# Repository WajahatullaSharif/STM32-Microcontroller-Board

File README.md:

# DeskNode-F4: Desk Automation Node

**DeskNode-F4** is an intelligent, high-current desk automation controller designed to eliminate phantom standby power and manage workspace environments dynamically. Built around the **STM32F407VGT6** microcontroller, the board intercepts host sleep/wake signals to automatically switch power rails for major workspace appliances and custom peripherals.

---

## 📊 System Architecture Block Diagram

```mermaid
graph TD
    %% Styling Configuration
    classDef mcu fill:#1b4d3e,stroke:#333,stroke-width:1.5px,color:#fff;
    classDef power fill:#d4af37,stroke:#333,stroke-width:1px,color:#000;
    classDef peripheral fill:#e1f5fe,stroke:#0288d1,stroke-width:1px,color:#000;
    classDef external fill:#f5f5f5,stroke:#616161,stroke-width:1px,color:#000;

    %% Central PCBA
    subgraph DeskNode_F4 [DeskNode-F4]
        DEBUGGER[STM32F103 Debugger]:::mcu
        MCU[STM32F407 MCU]:::mcu
        ETH[DP83826 PHY]:::peripheral
        LED_DRV[LED Driver ~5A]:::peripheral
        SENSE[Shunt + Op-Amp]:::peripheral
        RELAY_DRV[Relay Drivers]:::peripheral
    end

    %% Left-Side Power Inputs
    USB_OTG[OTG USB]:::power
    USB_DEB[Debug USB]:::power

    %% External Systems
    subgraph Laptop_Host [Laptop Host]
        LAPTOP[Laptop PC]:::external
    end

    subgraph AC_Loads [AC Mains Loads]
        LOADS[Monitors/Speakers/Other]:::external
    end

    %% Invisible spacer layout trick to push AC Loads down
    Laptop_Host ~~~ AC_Loads

    %% Left-Side Power Routing Layout
    USB_OTG -->|Power Input| MCU
    USB_DEB --> DEBUGGER
    DEBUGGER -->|Debug/Power| MCU
    
    %% Right-Side Power Routing Layout
    12V[12V Adaptor]:::power -->|DC Jack| LED_DRV

    %% Communication & Interface Links
    LAPTOP -->|Ethernet Link| ETH
    ETH <-->|RMII| MCU
    LAPTOP -->|USB CDC| MCU

    %% Output Paths
    MCU -->|PWM| LED_DRV -->|JST| STRIP[RGB LED Strip]:::external
    STRIP -->|Return| SENSE -->|Analog| MCU
    MCU -->|GPIO| RELAY_DRV -->|Control| AC_Loads
```

---

## 🛠️ System Architecture Overview

The core of the system is a custom **4-layer PCB** configured with a high-integrity stackup (**Signal / GND / Power / Signal**) to isolate sensitive analog paths from high-power switching transients.

### Onboard Hardware Features
* **Microcontroller:** STM32F407 ARM Cortex-M4 operating with a high-performance clock tree to coordinate networking, USB stacks, and deterministic control loops.
* **Onboard Debugger:** Integrated STM32F103-based DAP-Link. This permits single-cable firmware flashing and debugging directly over the `Debug USB` port without requiring external programmers.
* **Networking Subsystem:** DP83826 Physical Layer (PHY) transceiver linked to the MCU via a low-pin-count **RMII (Reduced Media Independent Interface)** bus. It provides a dedicated pipeline for sending continuous telemetry and log metrics to an external server or logging application.
* **Dual Power Inputs:** Flexible bus powering options allow the system logic to run entirely off the `Debugger USB (5V)` line or the primary `OTG USB (5V)` interface.

### Peripheral Control & Telemetry Loops
* **High-Current LED Driver:** A dedicated ~5A PWM driver stage capable of dimming and driving dense RGB LED strips utilized for monitor backlighting.
* **Current Telemetry (Shunt + Op-Amp):** A low-side inline current shunt paired with a precision operational amplifier provides analog current sensing feedback directly to the MCU's internal ADC. This ensures overload protection and active power calculation.
* **Relay Driver Array:** Low-voltage GPIO pins drive transistor/optocoupler stages to switch external heavy-duty AC relay modules safely.

---

## 🔄 Sequence of Operation

The system functions on a deterministic host-state monitoring loop via a virtual COM port over USB:

| Laptop State | USB CDC Pipeline | DeskNode-F4 Action |
| :--- | :--- | :--- |
| **Laptop Wakes** | Sends `"WAKE"` Token | 1. Latches AC Relays **ON** <br> 2. Ramps up Monitor LED Strip and Speakers |
| **Laptop Sleeps** | CDC Connection Drops | 1. Unlatches AC Relays **OFF** <br> 2. Cuts LED Strip Power |

### 1. The Wake Sequence (Power-On)
1. The host laptop wakes from standby or a sleep state.
2. An automation daemon running on the host detects the system state change and establishes a **USB CDC (Communications Device Class)** virtual serial connection.
3. The host transmits a configuration/activation token to the `DeskNode-F4` over USB.
4. The MCU immediately asserts its control GPIOs:
    * **Relay Output Pins** transition to high, latching the AC relay modules to deliver mains power simultaneously to **Monitor 1, Monitor 2, the Laptop Power Adaptor, and the Home Theatre System**.
    * **PWM Driver** initializes to ramp up the RGB backlight strip to the user's preferred brightness level via the onboard JST connection.

### 2. Continuous Monitoring State
* While active, the board uses the **DP83826 Ethernet PHY** to broadcast runtime diagnostics (uptime, temperature, and power drawing conditions) back to the laptop's logging software.
* The internal ADC continuously updates using the operational amplifier feedback loop across the shunt resistor to verify the current draw of the 5A LED string remains within a safe operating safe area (SOA).

### 3. The Sleep Sequence (Zero-Standby Power)
1. The host laptop enters a low-power sleep mode or is shut down.
2. The active USB CDC bus is dropped or broadcasts a graceful shutdown command packet.
3. Upon detecting the drop in the USB connection state, the `STM32F407` executes an emergency environment teardown:
    * All **GPIO Relay Driver lines** drop low, physically disconnecting the mains AC power lines. This drops the idle standby current consumption of the entire desk setup (monitors, sound systems, bricks) down to **absolute zero**.
    * The LED driver PWM is pulled to a 0% duty cycle, turning off the backlight completely.
    * The board drops into a low-power listening loop, drawing minimal parasitic power through the connected USB line until the next wake event.

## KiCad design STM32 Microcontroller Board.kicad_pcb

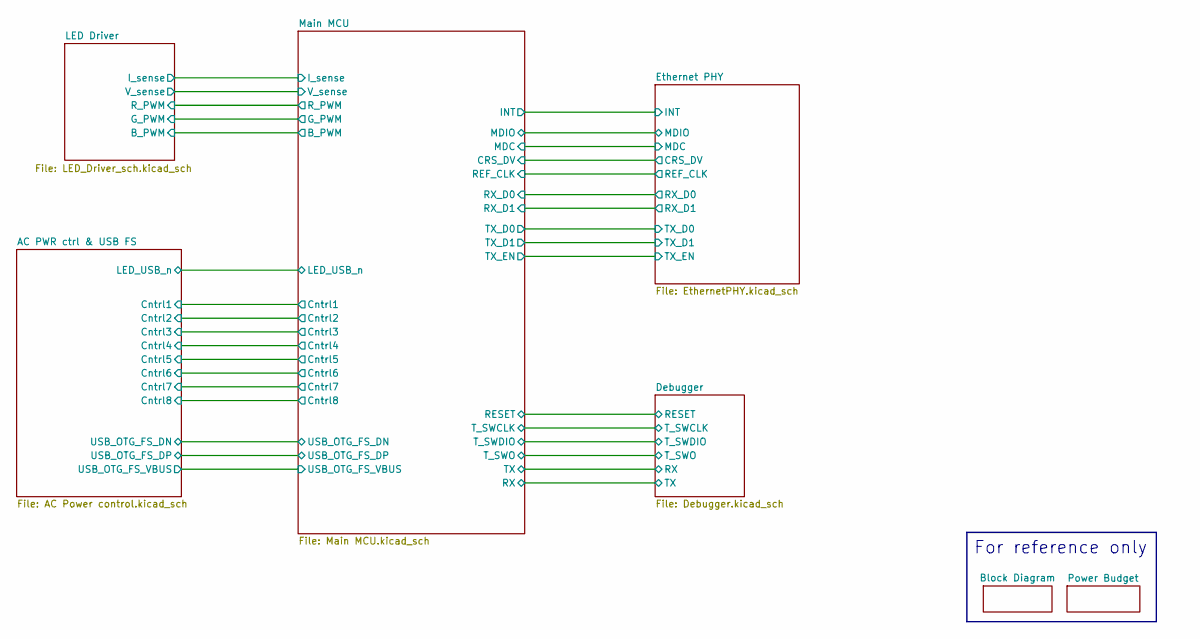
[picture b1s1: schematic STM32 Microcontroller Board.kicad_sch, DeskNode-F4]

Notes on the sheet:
For reference only

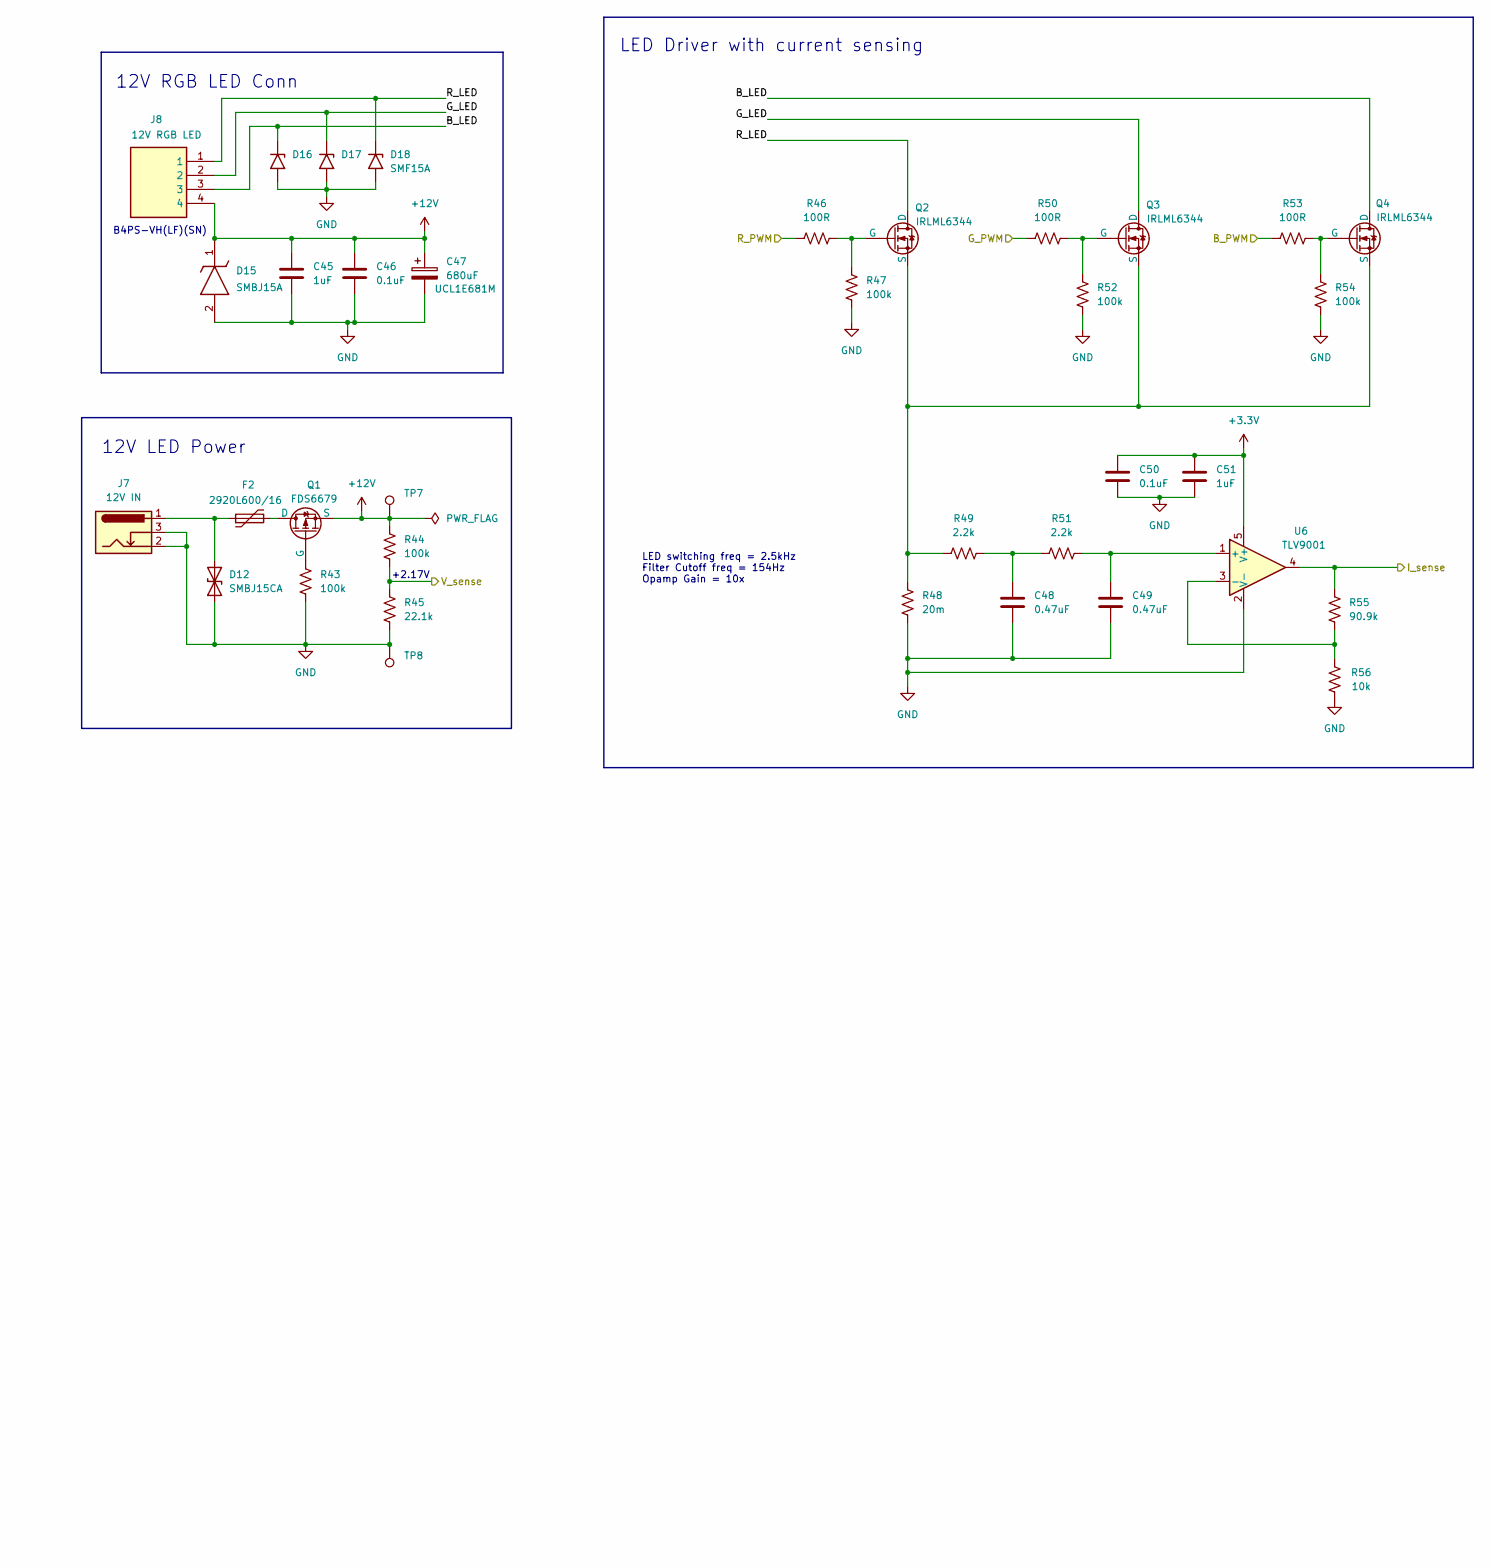
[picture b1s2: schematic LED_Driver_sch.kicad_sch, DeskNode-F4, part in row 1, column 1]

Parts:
C45: 1uF; C_0603_1608Metric; MPN CC0603KRX7R9BB105
C46: 0.1uF; C_0603_1608Metric; MPN C0603C104K5RACTU
C47: 680uF; UCL1E681MNL1GS; MPN UCL1E681MNL1GS
C48, C49: 0.47uF; C_0603_1608Metric; MPN CL10B474KA8NFNC
C50: 0.1uF; C_0402_1005Metric; MPN GRM155R71A104KA01D
C51: 1uF; C_0603_1608Metric; MPN CL10B105KP8NNNC
D12: SMBJ15CA; SMBJ15A; MPN SMBJ15CA
D15: SMBJ15A; Mouser Part Number 576-SMBJ15A
D16, D17, D18: SMF15A; D_SMF; MPN SMF15A
F2: Polyfuse; Fuse_2920_7451Metric; MPN 2920L600/16MR
J7: 12V IN; BarrelJack_Horizontal
J8: 12V RGB LED; B4PS-VH; Mouser Part Number 306-B4PS-VHLFSN
Q1: PMOS; SOIC-8_5.3x5.3mm_P1.27mm; Manufacturer_Part_Number FDS6679
Q2, Q3, Q4: NMOS; SOT-23; MPN IRLML6344TRPBF
R43, R44, R47, R52, R54: 100k; R_0603_1608Metric; MPN RC0603FR-07100KL
R45: 22.1k; R_0603_1608Metric; MPN RC0603FR-0722K1L
R46, R50, R53: 100R; R_0603_1608Metric; MPN RC0603FR-07100RL
R48: 20m; R_2512_6332Metric; MPN CRA2512-FZ-R020ELF
R49, R51: 2.2k; R_0603_1608Metric; MPN RC0603FR-072K2L
R55: 90.9k; R_0603_1608Metric; MPN RC0603FR-0790K9L
R56: 10k; R_0603_1608Metric; MPN RC0603FR-0710KL
TP7, TP8: TestPoint; TestPoint_Keystone_5000-5004_Miniature; MPN 5001
U6: TLV9001TIDCKR; SOT-353_SC-70-5; MPN TLV9001TIDCKR

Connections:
+3.3V: C50.1, C51.1, U6.5 (V+); also elsewhere on the board
+12V: C45.1, C46.1, C47.1, D15.1 (K), J8.4, Q1.2 (S), R44.1, TP7.1; also elsewhere on the board
/LED Driver/B_LED: D16.1 (A1), J8.3, Q4.1 (D)
/LED Driver/B_PWM: R53.1; also elsewhere on the board
/LED Driver/G_LED: D17.1 (A1), J8.2, Q3.1 (D)
/LED Driver/G_PWM: R50.1; also elsewhere on the board
/LED Driver/I_sense: R55.2, U6.4; also elsewhere on the board
/LED Driver/R_LED: D18.1 (A1), J8.1, Q2.1 (D)
/LED Driver/R_PWM: R46.1; also elsewhere on the board
/Main MCU/PB1: R44.2, R45.1; also elsewhere on the board
GND: C45.2, C46.2, C47.2, C48.2, C49.1, C50.2, C51.2, D12.1 (A1), D15.2 (A), D16.2 (A2), D17.2 (A2), D18.2 (A2), J7.2, J7.3, R43.2, R45.2, R47.2, R48.2, R52.2, R54.2, R56.1, TP8.1, U6.2 (V-); also elsewhere on the board
unnamed: C48.1, R49.2, R51.1
unnamed: D12.2 (A2), F2.1, J7.1
unnamed: F2.2, Q1.3 (D)
unnamed: Q1.1 (G), R43.1
unnamed: Q2.2 (G), R46.2, R47.1
unnamed: Q2.3 (S), Q3.3 (S), Q4.3 (S), R48.1, R49.1
unnamed: Q3.2 (G), R50.2, R52.1
unnamed: Q4.2 (G), R53.2, R54.1
unnamed: C49.2, R51.2, U6.1 (+)
unnamed: R55.1, R56.2, U6.3 (-)

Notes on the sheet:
+2.17V
LED switching freq = 2.5kHz Filter Cutoff freq = 154Hz Opamp Gain = 10x
12V LED Power
12V RGB LED Conn
LED Driver with current sensing
B4PS-VH(LF)(SN)

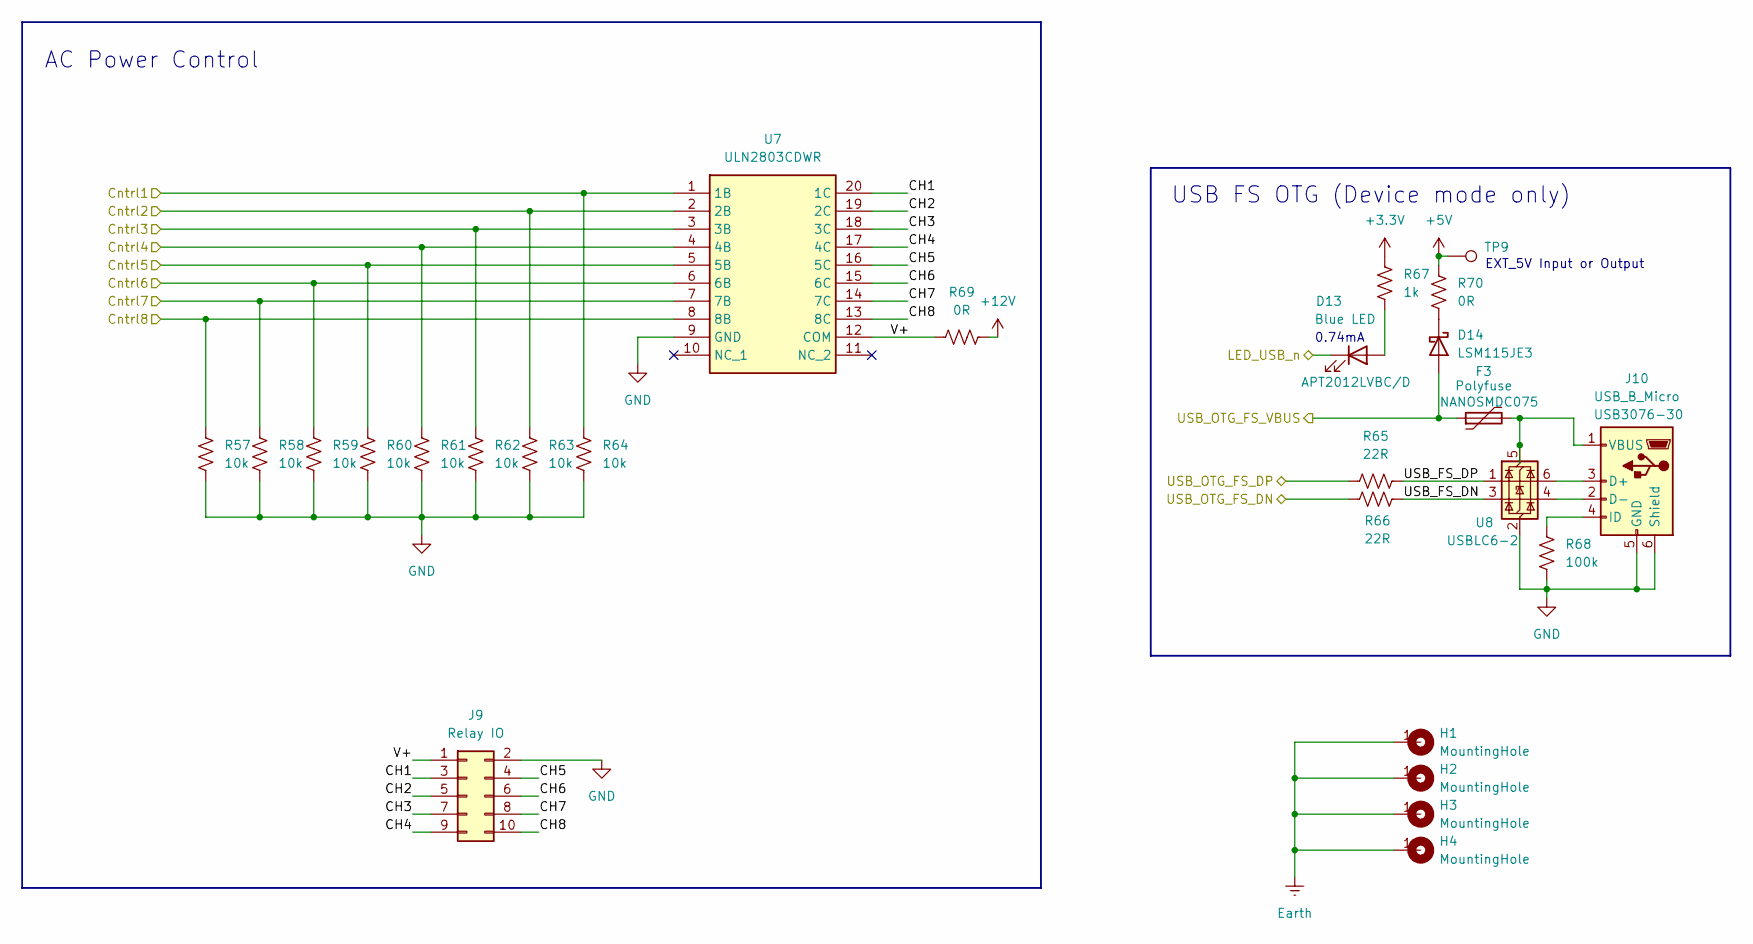
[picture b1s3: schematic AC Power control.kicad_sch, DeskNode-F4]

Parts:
D13: Blue LED; LED_0805_2012Metric; MPN APT2012LVBC/D
D14: LSM115JE3; D_SMB; MPN LSM115JE3-TR13
F3: Polyfuse; Fuse_1206_3216Metric; MPN NANOSMDC075F-2
H1, H2, H3, H4: MountingHole; MountingHole_3.2mm_M3_Pad
J9: Relay IO; PinHeader_2x05_P2.54mm_Vertical
J10: USB_B_Micro; USB_Micro-B_GCT_USB3076-30-A; MPN USB3076-30-A
R57, R58, R59, R60, R61, R62, R63, R64: 10k; R_0603_1608Metric; MPN RC0603FR-0710KL
R65, R66: 22R; R_0603_1608Metric; MPN RC0603FR-0722RL
R67: 1k; R_0603_1608Metric; MPN RC0603FR-071KL
R68: 100k; R_0603_1608Metric; MPN RC0603FR-07100KL
R69, R70: 0R; R_0603_1608Metric; MPN RC0603JR-070RL
TP9: TestPoint; TestPoint_Keystone_5000-5004_Miniature; MPN 5001
U7: ULN2803CDWR; Mouser Part Number 595-ULN2803CDWR
U8: USBLC6-2; SOT-23-6; MPN USBLC6-2SC6

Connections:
+3.3V: R67.1; also elsewhere on the board
+5V: R70.2, TP9.1; also elsewhere on the board
+12V: R69.2; also elsewhere on the board
/AC PWR ctrl & USB FS/CH1: J9.3, U7.20 (1C)
/AC PWR ctrl & USB FS/CH2: J9.5, U7.19 (2C)
/AC PWR ctrl & USB FS/CH3: J9.7, U7.18 (3C)
/AC PWR ctrl & USB FS/CH4: J9.9, U7.17 (4C)
/AC PWR ctrl & USB FS/CH5: J9.4, U7.16 (5C)
/AC PWR ctrl & USB FS/CH6: J9.6, U7.15 (6C)
/AC PWR ctrl & USB FS/CH7: J9.8, U7.14 (7C)
/AC PWR ctrl & USB FS/CH8: J9.10, U7.13 (8C)
/AC PWR ctrl & USB FS/Cntrl1: R64.1, U7.1 (1B); also elsewhere on the board
/AC PWR ctrl & USB FS/Cntrl2: R63.1, U7.2 (2B); also elsewhere on the board
/AC PWR ctrl & USB FS/Cntrl3: R62.1, U7.3 (3B); also elsewhere on the board
/AC PWR ctrl & USB FS/Cntrl4: R61.1, U7.4 (4B); also elsewhere on the board
/AC PWR ctrl & USB FS/Cntrl5: R60.1, U7.5 (5B); also elsewhere on the board
/AC PWR ctrl & USB FS/Cntrl6: R59.1, U7.6 (6B); also elsewhere on the board
/AC PWR ctrl & USB FS/Cntrl7: R58.1, U7.7 (7B); also elsewhere on the board
/AC PWR ctrl & USB FS/Cntrl8: R57.1, U7.8 (8B); also elsewhere on the board
/AC PWR ctrl & USB FS/LED_USB_n: D13.1 (K); also elsewhere on the board
/AC PWR ctrl & USB FS/USB_FS_DN: R66.2, U8.3 (I/O2)
/AC PWR ctrl & USB FS/USB_FS_DP: R65.1, U8.1 (I/O1)
/AC PWR ctrl & USB FS/USB_OTG_FS_DN: R66.1; also elsewhere on the board
/AC PWR ctrl & USB FS/USB_OTG_FS_DP: R65.2; also elsewhere on the board
/AC PWR ctrl & USB FS/USB_OTG_FS_VBUS: D14.2 (A), F3.1; also elsewhere on the board
/AC PWR ctrl & USB FS/V+: J9.1, R69.1, U7.12 (COM)
Earth: H1.1, H2.1, H3.1, H4.1; also elsewhere on the board
GND: J9.2, J10.5 (GND), J10.6 (Shield), R57.2, R58.2, R59.2, R60.2, R61.2, R62.2, R63.2, R64.2, R68.1, U7.9 (GND), U8.2 (GND); also elsewhere on the board
unnamed: D13.2 (A), R67.2
unnamed: D14.1 (K), R70.1
unnamed: J10.3 (D+), U8.6 (I/O1)
unnamed: J10.2 (D-), U8.4 (I/O2)
unnamed: J10.4 (ID), R68.2
unnamed: F3.2, J10.1 (VBUS), U8.5 (VBUS)

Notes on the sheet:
USB FS OTG (Device mode only)
EXT_5V Input or Output
AC Power Control
0.74mA

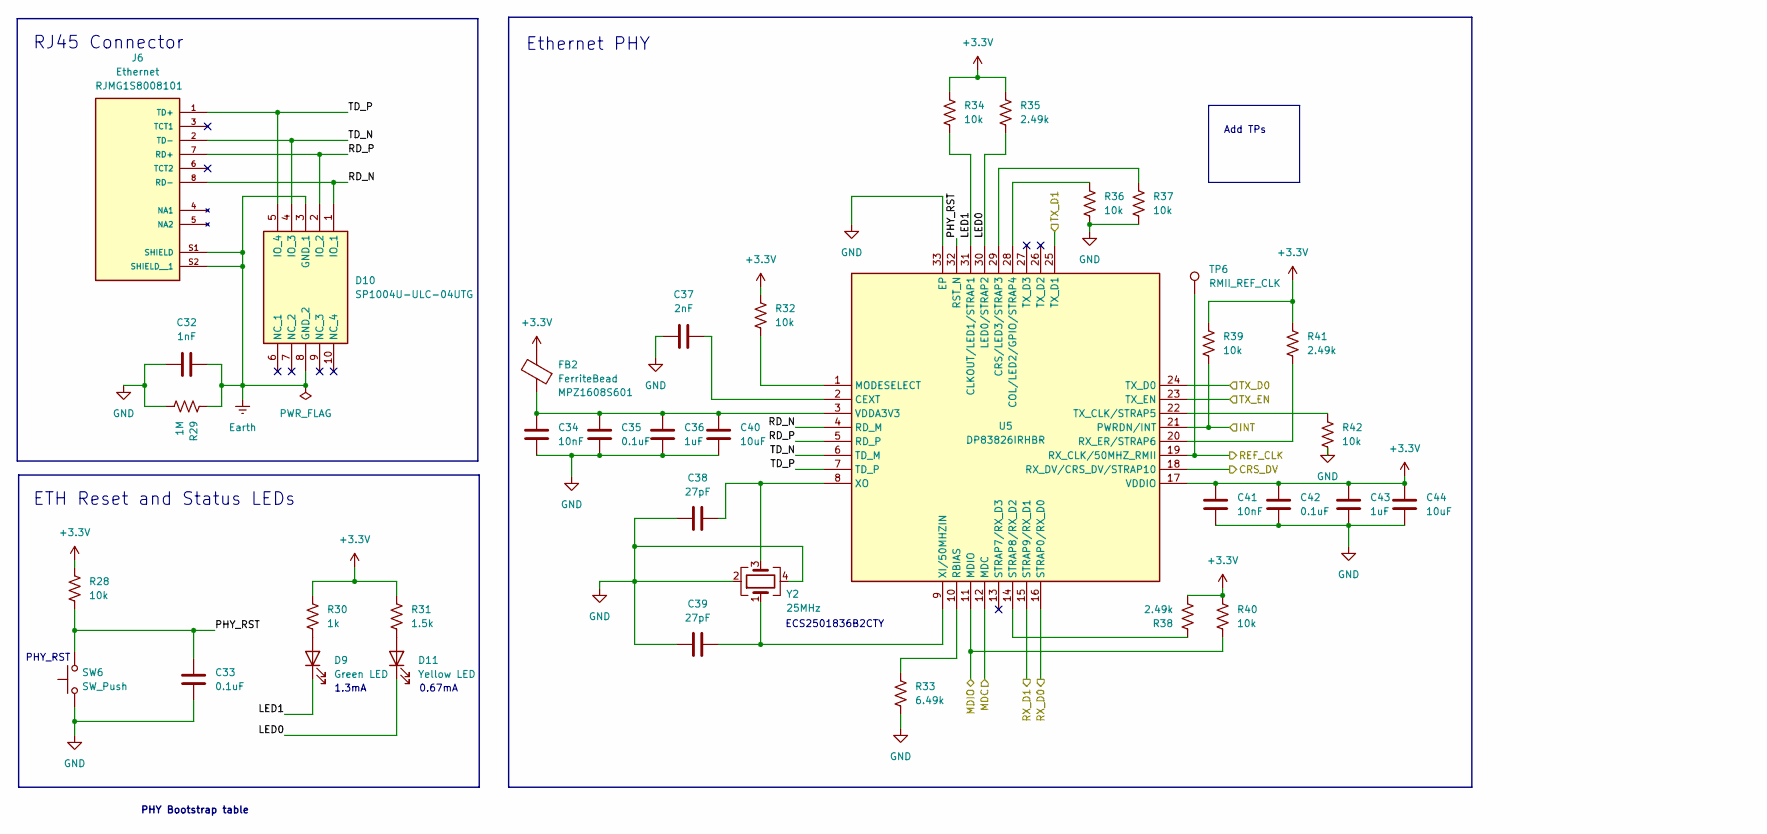
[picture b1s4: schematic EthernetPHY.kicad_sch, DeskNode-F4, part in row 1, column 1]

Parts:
C32: 1nF; C_1206_3216Metric; MPN CC1206KKX7RDBB102
C33, C35, C42: 0.1uF; C_0402_1005Metric; MPN GRM155R71A104KA01D
C34, C41: 10nF; C_0402_1005Metric; MPN GRM155R71E103KA01D
C36, C43: 1uF; C_0603_1608Metric; MPN CL10B105KP8NNNC
C37: 2nF; C_0603_1608Metric; MPN GRM1885C1H202JA01D
C38, C39: 27pF; C_0603_1608Metric; MPN CL10C270JB8NNNC
C40, C44: 10uF; C_0805_2012Metric; Manufacturer_Part_Number GRM21BR71A106KA73L
D9: Green LED; LED_0805_2012Metric; MPN APT2012CGCK
D10: SP1004U-ULC-04UTG; ESD8104MUTAG; MPN SP1004U-ULC-04UTG
D11: Yellow LED; LED_0805_2012Metric; MPN APT2012SYCK
FB2: FerriteBead; L_0603_1608Metric; MPN MPZ1608S601ATA00
J6: Ethernet; AMPHENOL_RJMG1S8008101BR; PARTREV A
R28, R32, R34, R36, R37, R39, R40, R42: 10k; R_0603_1608Metric; MPN RC0603FR-0710KL
R29: 1M; R_0603_1608Metric; MPN RC0603FR-071ML
R30: 1k; R_0603_1608Metric; MPN RC0603FR-071KL
R31: 1.5k; R_0603_1608Metric; MPN RC0603FR-071K5L
R33: 6.49k; R_0603_1608Metric; MPN RC0603FR-076K49L
R35, R38, R41: 2.49k; R_0603_1608Metric; MPN RC0603FR-072K49L
SW6: SW_Push; SW_SPST_PTS645Sx43SMTR92; MPN SWT0310-043016GSA
TP6: RMII_REF_CLK; TestPoint_Pad_D1.0mm
U5: DP83826IRHBR; QFN50P500X500X100-33N-D; Mouser Part Number 595-DP83826IRHBR
Y2: 25MHz; ECS2501836B2CTYTR; Mouser Part Number 520-250-18-36B2CTYTR

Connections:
+3.3V: C41.1, C42.1, C43.1, C44.1, FB2.2, R28.1, R30.1, R31.2, R32.1, R34.1, R35.1, R38.1, R39.1, R40.1, R41.1, U5.17 (VDDIO); also elsewhere on the board
/Ethernet PHY/CRS_DV: U5.18 (RX_DV/CRS_DV/STRAP10); also elsewhere on the board
/Ethernet PHY/INT: R39.2, U5.21 (PWRDN/INT); also elsewhere on the board
/Ethernet PHY/LED0: D11.1 (K), R35.2, U5.30 (LED0/STRAP2)
/Ethernet PHY/LED1: D9.1 (K), R34.2, U5.31 (CLKOUT/LED1/STRAP1)
/Ethernet PHY/MDC: U5.12 (MDC); also elsewhere on the board
/Ethernet PHY/MDIO: R40.2, U5.11 (MDIO); also elsewhere on the board
/Ethernet PHY/PHY_RST: C33.1, R28.2, SW6.2, U5.32 (RST_N)
/Ethernet PHY/RD_N: D10.1 (IO_1), J6.8 (RD-), U5.4 (RD_M)
/Ethernet PHY/RD_P: D10.2 (IO_2), J6.7 (RD+), U5.5 (RD_P)
/Ethernet PHY/REF_CLK: TP6.1, U5.19 (RX_CLK/50MHZ_RMII); also elsewhere on the board
/Ethernet PHY/RX_D0: U5.16 (STRAP0/RX_D0); also elsewhere on the board
/Ethernet PHY/RX_D1: U5.15 (STRAP9/RX_D1); also elsewhere on the board
/Ethernet PHY/TD_N: D10.4 (IO_3), J6.2 (TD-), U5.6 (TD_M)
/Ethernet PHY/TD_P: D10.5 (IO_4), J6.1 (TD+), U5.7 (TD_P)
/Ethernet PHY/TX_D0: U5.24 (TX_D0); also elsewhere on the board
/Ethernet PHY/TX_D1: U5.25 (TX_D1); also elsewhere on the board
/Ethernet PHY/TX_EN: U5.23 (TX_EN); also elsewhere on the board
Earth: C32.2, D10.3 (GND_1), D10.8 (GND_2), J6.S1 (SHIELD), J6.S2 (SHIELD__1), R29.2; also elsewhere on the board
GND: C32.1, C33.2, C34.2, C35.2, C36.2, C37.1, C38.1, C39.1, C40.2, C41.2, C42.2, C43.2, C44.2, R29.1, R33.1, R36.2, R37.2, R42.2, SW6.1, U5.33 (EP), Y2.2, Y2.4; also elsewhere on the board
unnamed: D9.2 (A), R30.2
unnamed: D11.2 (A), R31.1
unnamed: C37.2, U5.2 (CEXT)
unnamed: R36.1, U5.28 (COL/LED2/GPIO/STRAP4)
unnamed: R37.1, U5.29 (CRS/LED3/STRAP3)
unnamed: R32.2, U5.1 (MODESELECT)
unnamed: R33.2, U5.10 (RBIAS)
unnamed: R41.2, U5.20 (RX_ER/STRAP6)
unnamed: R38.2, U5.14 (STRAP8/RX_D2)
unnamed: R42.1, U5.22 (TX_CLK/STRAP5)
unnamed: C34.1, C35.1, C36.1, C40.1, FB2.1, U5.3 (VDDA3V3)
unnamed: C39.2, U5.9 (XI/50MHZIN), Y2.1
unnamed: C38.2, U5.8 (XO), Y2.3

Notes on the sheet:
0.67mA
Add TPs
Ethernet PHY
ECS2501836B2CTY
PHY Bootstrap table
RJ45 Connector
1.3mA
PHY_RST
ETH Reset and Status LEDs

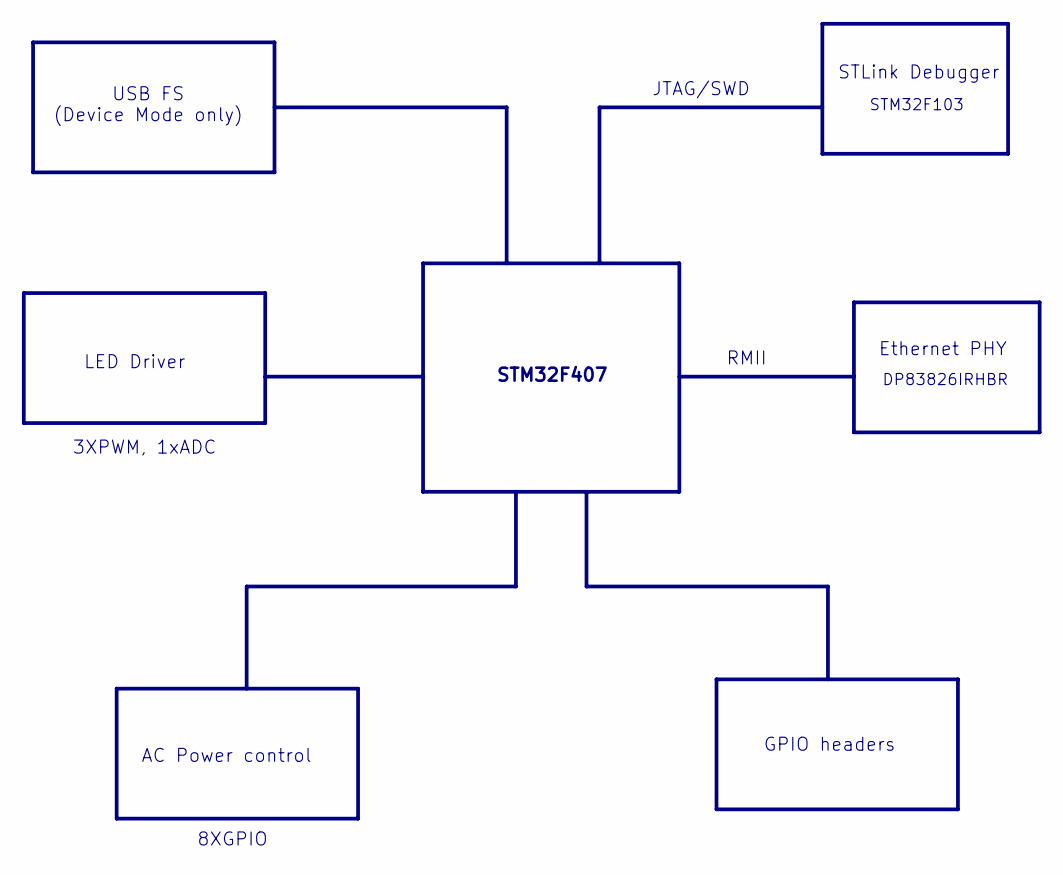
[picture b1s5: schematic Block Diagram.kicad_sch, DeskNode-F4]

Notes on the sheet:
DP83826IRHBR
STLink Debugger
LED Driver
JTAG/SWD
STM32F407
USB FS (Device Mode only)
GPIO headers
3XPWM, 1xADC
8XGPIO
STM32F103
Ethernet PHY
AC Power control
RMII

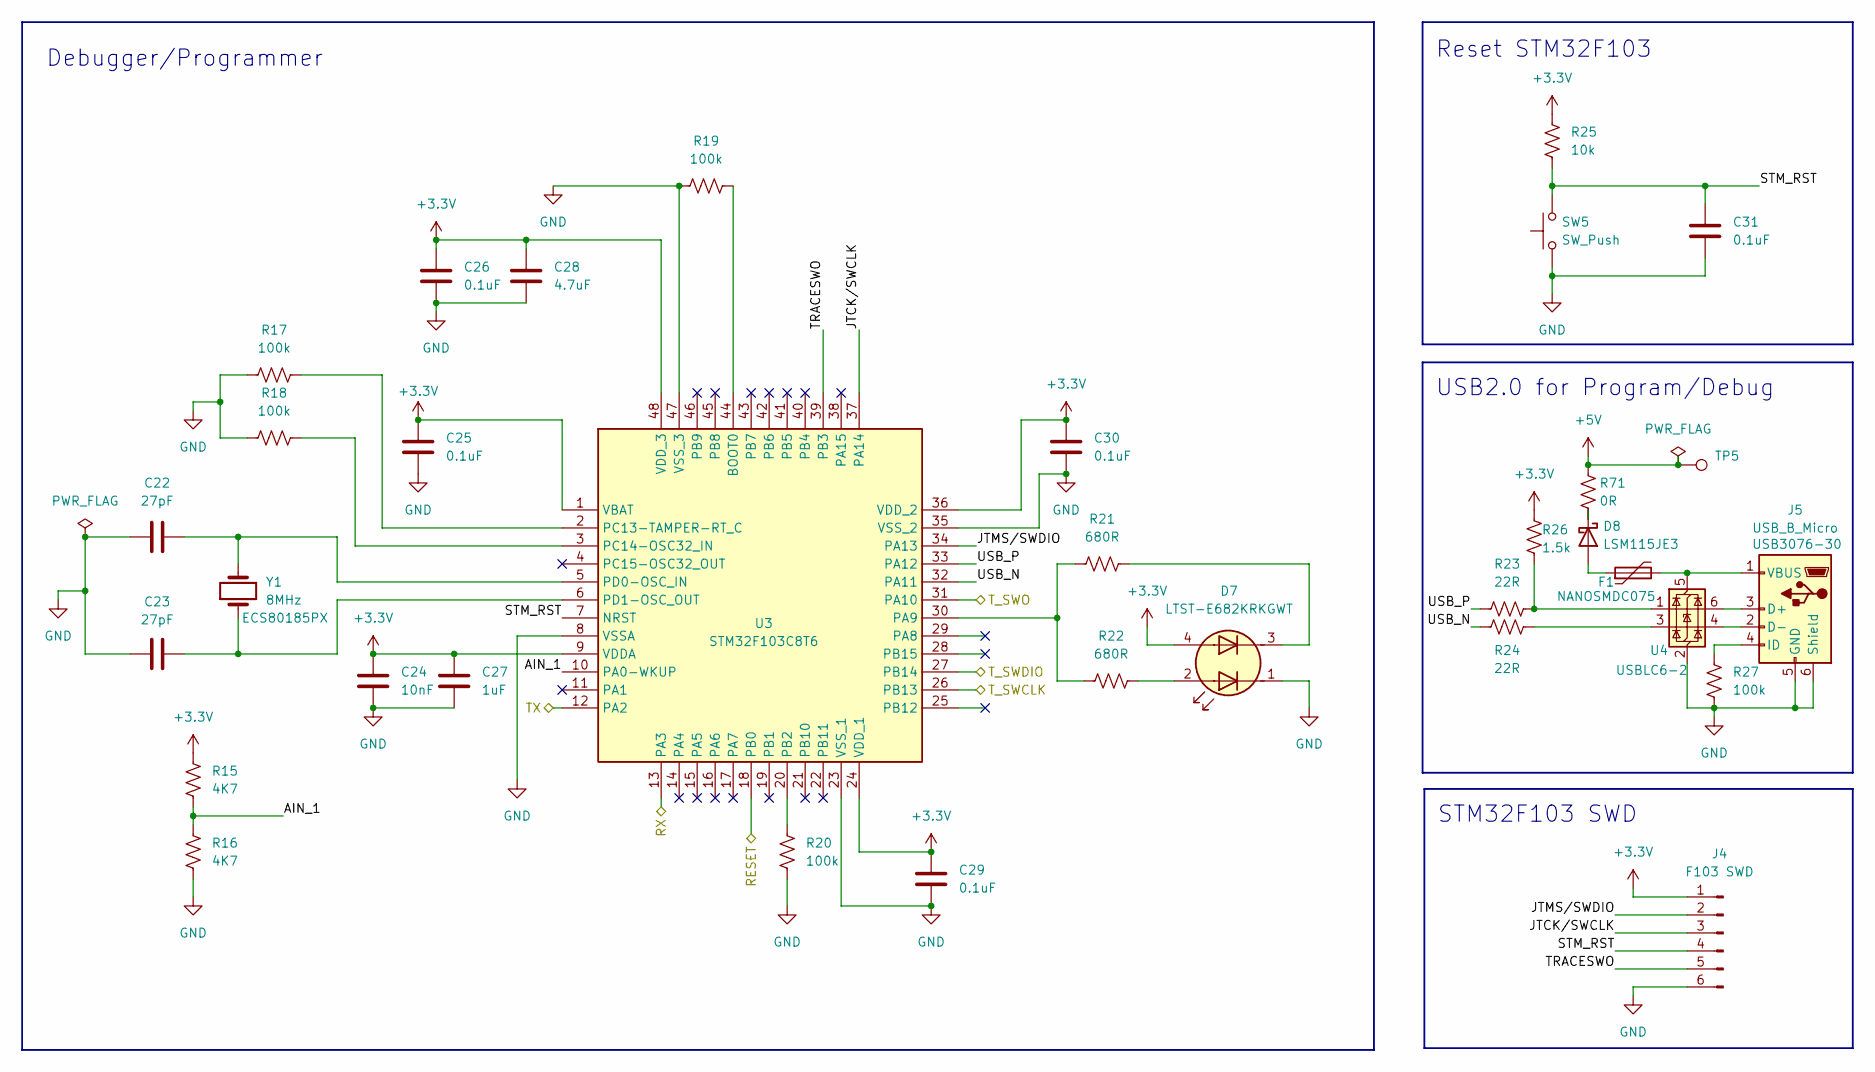
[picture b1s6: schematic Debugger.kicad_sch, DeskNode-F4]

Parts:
C22, C23: 27pF; C_0603_1608Metric; MPN CL10C270JB8NNNC
C24: 10nF; C_0402_1005Metric; MPN GRM155R71E103KA01D
C25, C26, C29, C30, C31: 0.1uF; C_0402_1005Metric; MPN GRM155R71A104KA01D
C27: 1uF; C_0603_1608Metric; MPN CL10B105KP8NNNC
C28: 4.7uF; C_0805_2012Metric; MPN GRM21BR71C475KE51L
D7: LTST-E682KRKGWT; LTSTE683RGBW; MPN LTST-E682KRKGWT
D8: LSM115JE3; D_SMB; MPN LSM115JE3-TR13
F1: Polyfuse; Fuse_1206_3216Metric; MPN NANOSMDC075F-2
J4: F103 SWD; PinHeader_1x06_P2.54mm_Vertical
J5: USB_B_Micro; USB_Micro-B_GCT_USB3076-30-A; MPN USB3076-30-A
R15, R16: 4K7; R_0603_1608Metric; MPN RC0603FR-074K7L
R17, R18, R19, R20, R27: 100k; R_0603_1608Metric; MPN RC0603FR-07100KL
R21, R22: 680R; R_0603_1608Metric; MPN RC0603FR-07680RL
R23, R24: 22R; R_0603_1608Metric; MPN RC0603FR-0722RL
R25: 10k; R_0603_1608Metric; MPN RC0603FR-0710KL
R26: 1.5k; R_0603_1608Metric; MPN RC0603FR-071K5L
R71: 0R; R_0603_1608Metric; MPN RC0603JR-070RL
SW5: SW_Push; SW_SPST_PTS645Sx43SMTR92; MPN SWT0310-043016GSA
TP5: TestPoint; TestPoint_Keystone_5000-5004_Miniature; MPN 5001
U3: STM32F103C8T6; QFP50P900X900X160-48N; Mouser Part Number 511-STM32F103C8T6
U4: USBLC6-2; SOT-23-6; MPN USBLC6-2SC6
Y1: 8MHz; Crystal_HC49-4H_Vertical; MPN ECS-80-18-5PX-TR

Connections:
+3.3V: C24.1, C25.1, C26.1, C27.1, C28.1, C29.1, C30.1, D7.4 (A2), J4.1, R15.2, R25.1, R26.1, U3.1 (VBAT), U3.9 (VDDA), U3.24 (VDD_1), U3.36 (VDD_2), U3.48 (VDD_3); also elsewhere on the board
+5V: R71.2, TP5.1; also elsewhere on the board
/Debugger/AIN_1: R15.1, R16.2, U3.10 (PA0-WKUP)
/Debugger/JTCK/SWCLK: J4.3, U3.37 (PA14)
/Debugger/JTMS/SWDIO: J4.2, U3.34 (PA13)
/Debugger/RX: U3.13 (PA3); also elsewhere on the board
/Debugger/STM_RST: C31.1, J4.4, R25.2, SW5.2, U3.7 (NRST)
/Debugger/TRACESWO: J4.5, U3.39 (PB3)
/Debugger/TX: U3.12 (PA2); also elsewhere on the board
/Debugger/USB_N: R24.1, U3.32 (PA11)
/Debugger/USB_P: R23.2, U3.33 (PA12)
/Main MCU/RESET: U3.18 (PB0); also elsewhere on the board
/Main MCU/T_SWCLK: U3.26 (PB13); also elsewhere on the board
/Main MCU/T_SWDIO: U3.27 (PB14); also elsewhere on the board
/Main MCU/T_SWO: U3.31 (PA10); also elsewhere on the board
GND: C22.1, C23.1, C24.2, C25.2, C26.2, C27.2, C28.2, C29.2, C30.2, C31.2, D7.1 (K1), J4.6, J5.5 (GND), J5.6 (Shield), R16.1, R17.1, R18.1, R19.1, R20.2, R27.1, SW5.1, U3.8 (VSSA), U3.23 (VSS_1), U3.35 (VSS_2), U3.47 (VSS_3), U4.2 (GND); also elsewhere on the board
unnamed: D7.2 (A1), R22.2
unnamed: D7.3 (K2), R21.2
unnamed: D8.2 (A), F1.1
unnamed: D8.1 (K), R71.1
unnamed: J5.3 (D+), U4.6 (I/O1)
unnamed: J5.2 (D-), U4.4 (I/O2)
unnamed: J5.4 (ID), R27.2
unnamed: F1.2, J5.1 (VBUS), U4.5 (VBUS)
unnamed: R23.1, R26.2, U4.1 (I/O1)
unnamed: R24.2, U4.3 (I/O2)
unnamed: R19.2, U3.44 (BOOT0)
unnamed: R21.1, R22.1, U3.30 (PA9)
unnamed: R20.1, U3.20 (PB2)
unnamed: R17.2, U3.2 (PC13-TAMPER-RT_C)
unnamed: R18.2, U3.3 (PC14-OSC32_IN)
unnamed: C22.2, U3.5 (PD0-OSC_IN), Y1.2
unnamed: C23.2, U3.6 (PD1-OSC_OUT), Y1.1

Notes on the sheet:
STM32F103 SWD
USB2.0 for Program/Debug
Reset STM32F103
Debugger/Programmer

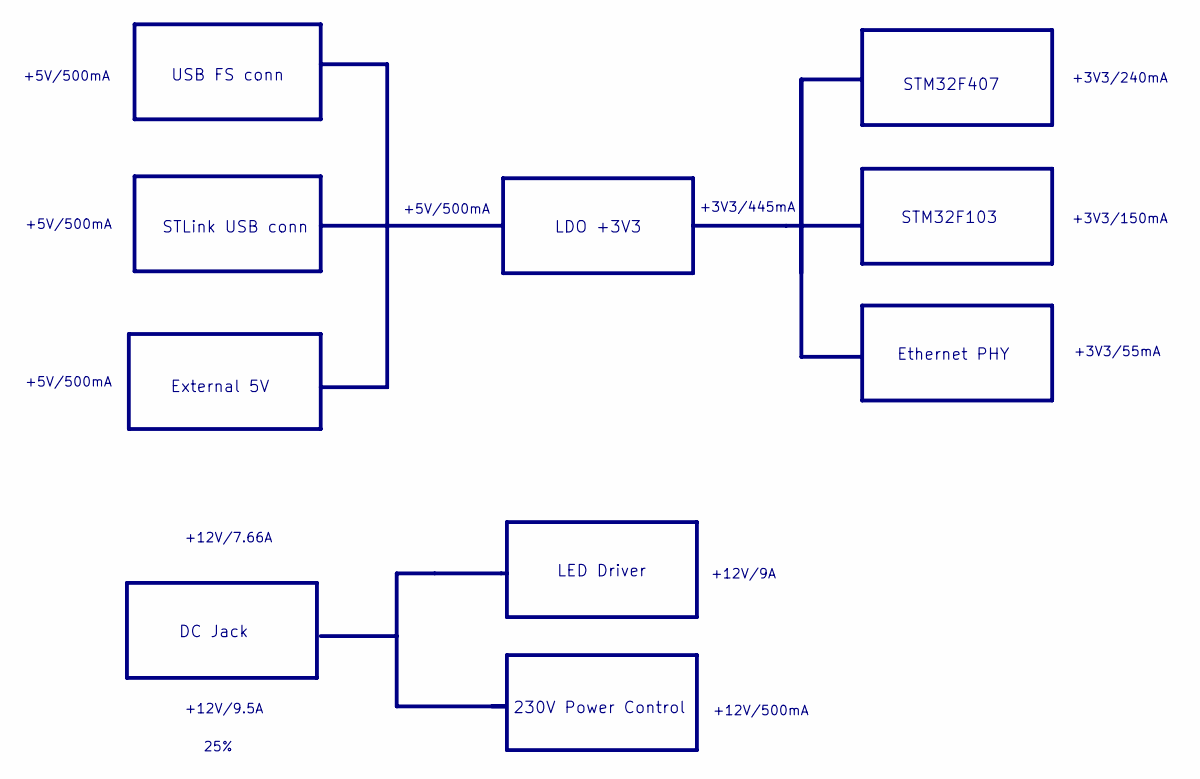
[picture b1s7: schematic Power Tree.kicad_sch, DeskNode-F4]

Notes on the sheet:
+12V/9A
External 5V
+5V/500mA
USB FS conn
230V Power Control
+12V/9.5A
LED Driver
+3V3/55mA
STM32F103
Ethernet PHY
+3V3/150mA
DC Jack
+12V/7.66A
25%
STM32F407
+12V/500mA
+3V3/240mA
LDO +3V3
+3V3/445mA
STLink USB conn
